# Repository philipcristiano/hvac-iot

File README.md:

# hvac-iot
IoT system for HVAC control

## Develop

Get Arduino CLI

See `.github/workflows/Arduino_Sensor.yml` for the most up to date steps

### Compile

```
arduino-cli compile --fqbn adafruit:samd:adafruit_feather_m0 Sensor

```

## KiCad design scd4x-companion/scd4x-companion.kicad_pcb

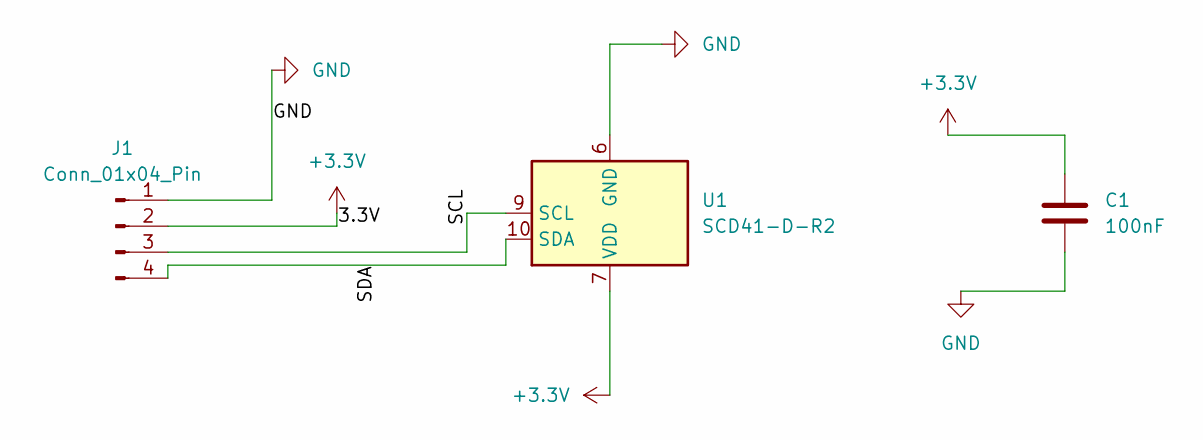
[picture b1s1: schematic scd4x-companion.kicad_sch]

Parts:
C1: 100nF; C_0603_1608Metric
J1: Conn_01x04_Pin; 1x04
U1: SCD41-D-R2; Sensirion_SCD4x-1EP_10.1x10.1mm_P1.25mm_EP4.8x4.8mm

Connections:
+3.3V: C1.1, J1.2, U1.7 (VDD), U1.19 (VDD)
/SCL: J1.3, U1.9 (SCL)
/SDA: J1.4, U1.10 (SDA)
GND: C1.2, J1.1, U1.6 (GND), U1.20 (GND), U1.21 (GND)

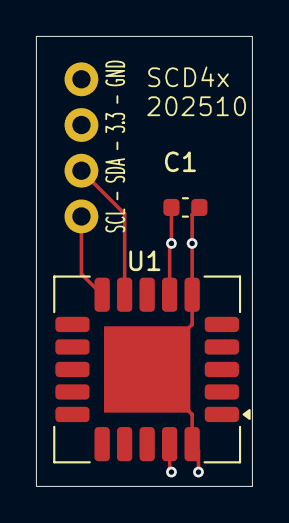
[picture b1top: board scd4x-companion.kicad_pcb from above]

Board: 2 copper layers, 12.0 x 25.0 mm, 3 parts (0 on the bottom side), 4 nets.

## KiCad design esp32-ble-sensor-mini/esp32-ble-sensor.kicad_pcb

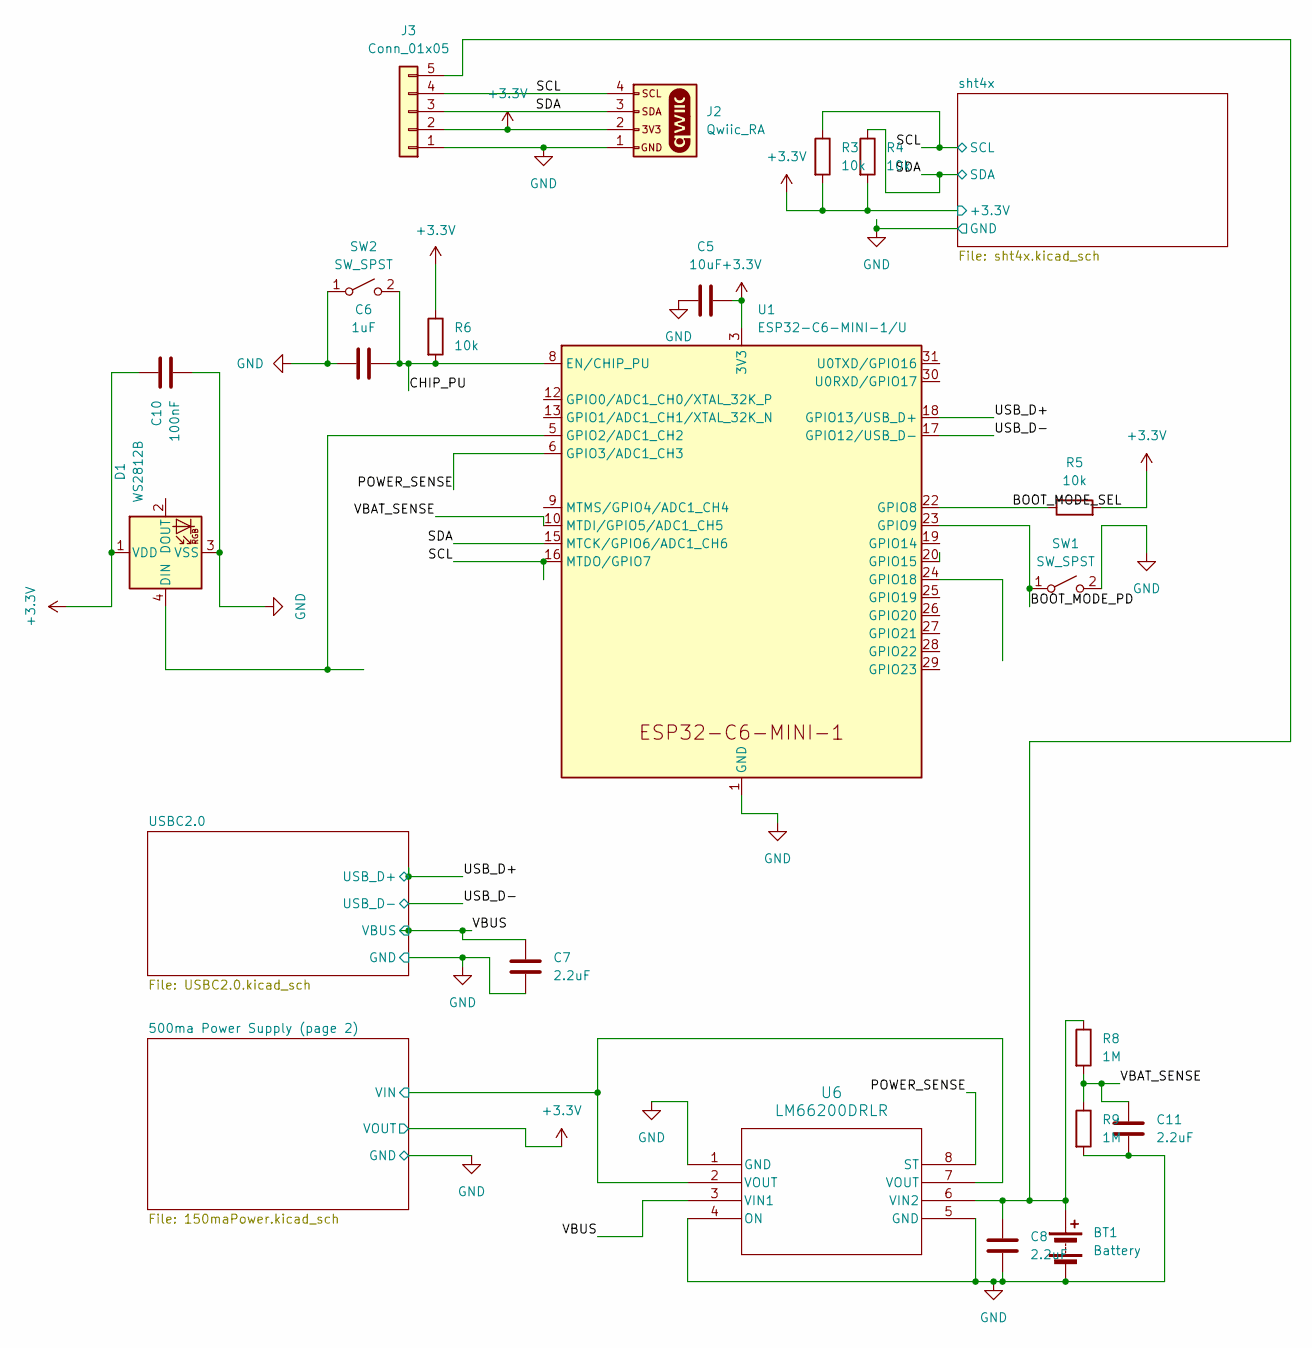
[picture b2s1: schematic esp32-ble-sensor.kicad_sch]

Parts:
BT1: Battery; BatteryHolder_Keystone_1042_1x18650
C5: 10uF; C_1206_3216Metric
C6: 1uF; C_1206_3216Metric
C7, C8, C11: 2.2uF; C_1206_3216Metric
C10: 100nF; C_0603_1608Metric
D1: WS2812B; LED_WS2812B_PLCC4_5.0x5.0mm_P3.2mm
J2: Qwiic_RA; JST_SMD_1.0mm-4_Black
J3: Conn_01x05; 1x05_Castellated
R3, R4, R5, R6: 10k; R_0603_1608Metric
R8, R9: 1M; R_0603_1608Metric
SW1, SW2: SW_SPST; SW_TS18-5-17-SL-260-SMT-TR
U1: ESP32-C6-MINI-1/U; ESP32-C6-MINI-1
U6: LM66200DRLR; SOT-5X3_DRL_TEX

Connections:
+3.3V: C5.2, C10.1, D1.1 (VDD), J2.2, J3.2, R3.2, R4.2, R5.2, R6.1, U1.3 (3V3); also elsewhere on the board
/500ma Power Supply (page 2)/VIN: U6.2 (VOUT), U6.7 (VOUT); also elsewhere on the board
/BOOT_MODE_PD: SW1.1 (A), U1.23 (GPIO9)
/BOOT_MODE_SEL: R5.1, U1.22 (GPIO8)
/CHIP_PU: C6.1, R6.2, SW2.2 (B), U1.8 (EN/CHIP_PU)
/POWER_SENSE: U1.6 (GPIO3/ADC1_CH3), U6.8 (ST)
/SCL: J2.4, J3.4, R3.1, U1.16 (MTDO/GPIO7); also elsewhere on the board
/SDA: J2.3, J3.3, R4.1, U1.15 (MTCK/GPIO6/ADC1_CH6); also elsewhere on the board
/USB_D+: U1.18 (GPIO13/USB_D+); also elsewhere on the board
/USB_D-: U1.17 (GPIO12/USB_D-); also elsewhere on the board
/VBAT_SENSE: C11.1, R8.2, R9.1, U1.10 (MTDI/GPIO5/ADC1_CH5)
/VBUS: C7.1, U6.3 (VIN1); also elsewhere on the board
GND: BT1.2 (-), C5.1, C6.2, C7.2, C8.2, C10.2, C11.2, D1.3 (VSS), J2.1, J3.1, R9.2, SW1.2 (B), SW2.1 (A), U1.1 (GND), U1.2 (GND), U1.11 (GND), U1.14 (GND), U1.36 (GND), U1.37 (GND), U1.38 (GND), U1.39 (GND), U1.40 (GND), U1.41 (GND), U1.42 (GND), U1.43 (GND), U1.44 (GND), U1.45 (GND), U1.46 (GND), U1.47 (GND), U1.48 (GND), U1.49 (GND), U1.50 (GND), U1.51 (GND), U1.52 (GND), U1.53 (GND), U6.1 (GND), U6.4 (ON), U6.5 (GND); also elsewhere on the board
unnamed: BT1.1 (+), C8.1, J3.5, R8.1, U6.6 (VIN2)
unnamed: D1.4 (DIN), U1.5 (GPIO2/ADC1_CH2)

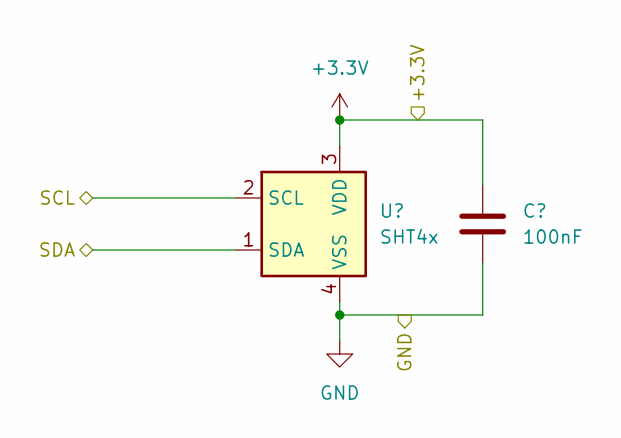
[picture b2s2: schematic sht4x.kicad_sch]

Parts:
C1: 100nF; C_0603_1608Metric
U2: SHT4x; Sensirion_DFN-4_1.5x1.5mm_P0.8mm_SHT4x_NoCentralPad

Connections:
+3.3V: C1.1, U2.3 (VDD); also elsewhere on the board
/SCL: U2.2 (SCL); also elsewhere on the board
/SDA: U2.1 (SDA); also elsewhere on the board
GND: C1.2, U2.4 (VSS); also elsewhere on the board

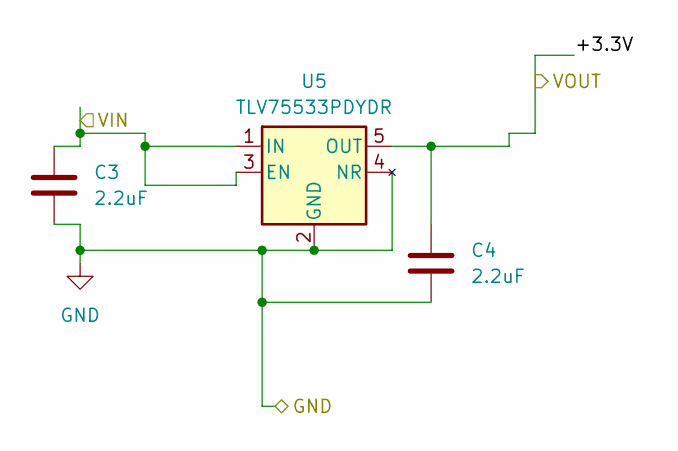
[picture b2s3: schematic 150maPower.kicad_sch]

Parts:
C3, C4: 2.2uF; C_1206_3216Metric
U5: TLV75533PDYDR; SOT-23-5

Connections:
+3.3V: C4.1, U5.5 (OUT); also elsewhere on the board
/500ma Power Supply (page 2)/VIN: C3.1, U5.1 (IN), U5.3 (EN); also elsewhere on the board
GND: C3.2, C4.2, U5.2 (GND), U5.4 (NR); also elsewhere on the board

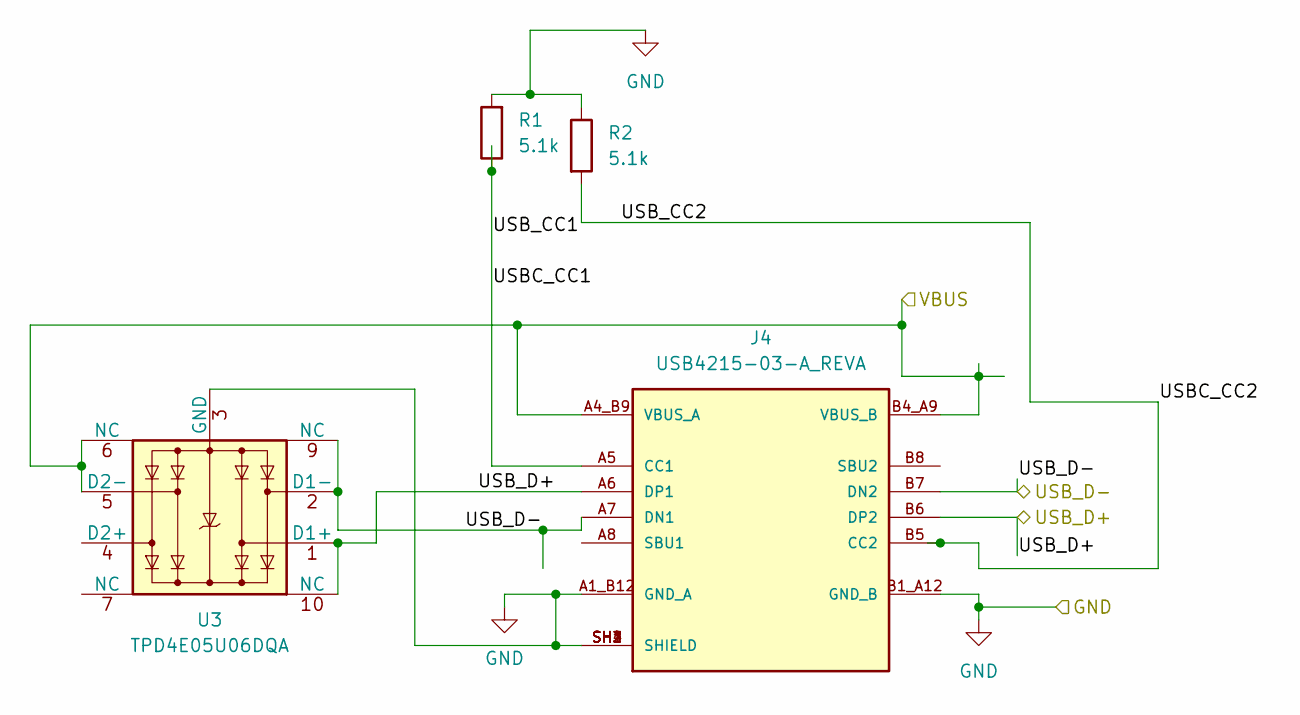
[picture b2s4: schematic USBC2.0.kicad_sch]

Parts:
J4: USB4215-03-A_REVA; GCT_USB4215-03-A_REVA; PARTREV A
R1, R2: 5.1k; R_0603_1608Metric
U3: TPD4E05U06DQA; USON-10_2.5x1.0mm_P0.5mm

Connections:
/USBC2.0/USBC_CC1: J4.A5 (CC1), R1.1
/USBC2.0/USBC_CC2: J4.B5 (CC2), R2.2
/USB_D+: J4.A6 (DP1), J4.B6 (DP2), U3.1 (D1+), U3.10 (NC); also elsewhere on the board
/USB_D-: J4.A7 (DN1), J4.B7 (DN2), U3.2 (D1-), U3.9 (NC); also elsewhere on the board
/VBUS: J4.A4_B9 (VBUS_A), J4.B4_A9 (VBUS_B), U3.5 (D2-), U3.6 (NC); also elsewhere on the board
GND: J4.A1_B12 (GND_A), J4.B1_A12 (GND_B), J4.SH1 (SHIELD), J4.SH2 (SHIELD), J4.SH3 (SHIELD), J4.SH4 (SHIELD), R1.2, R2.1, U3.3 (GND), U3.8 (GND); also elsewhere on the board

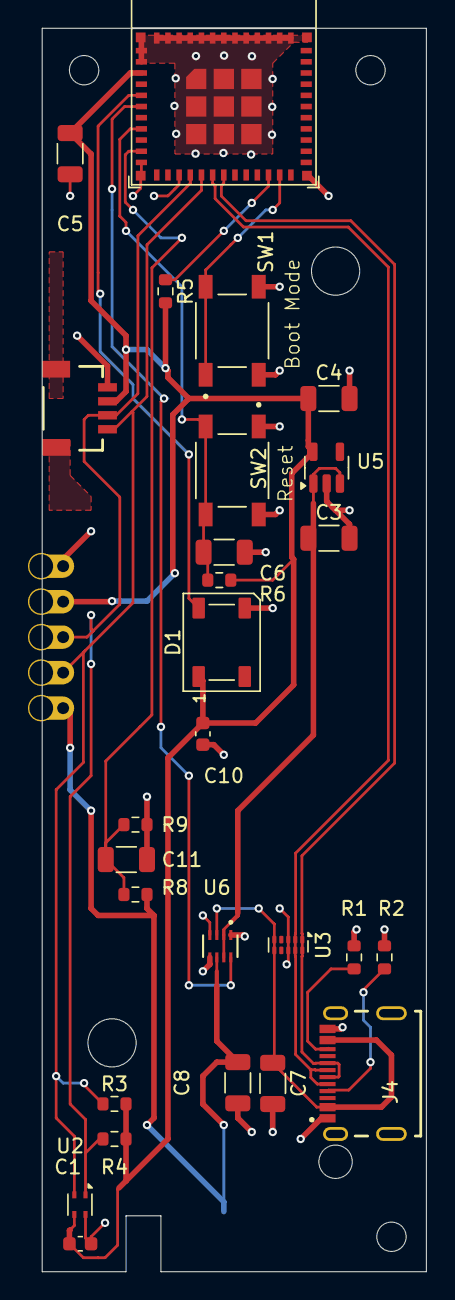
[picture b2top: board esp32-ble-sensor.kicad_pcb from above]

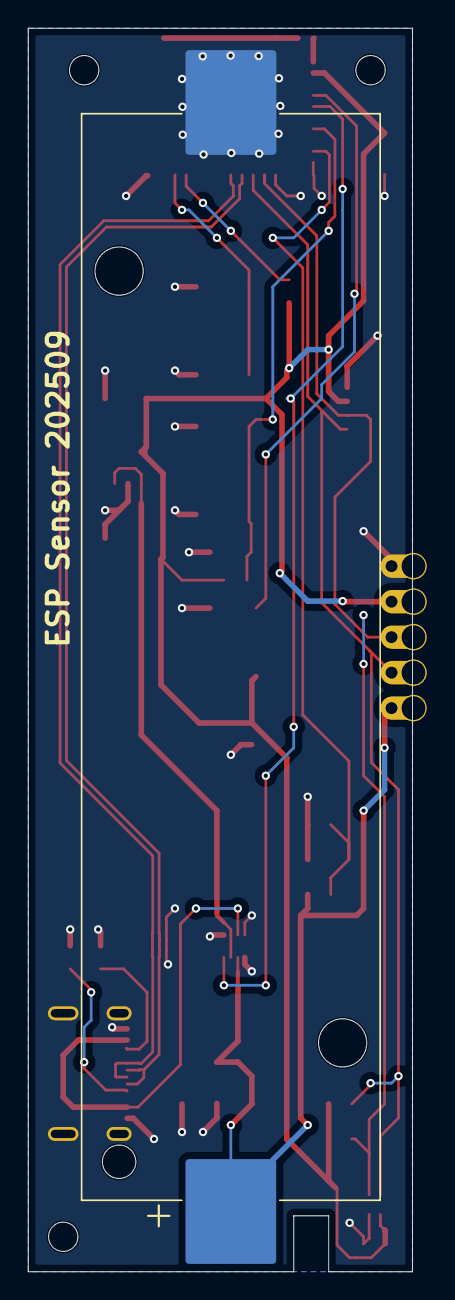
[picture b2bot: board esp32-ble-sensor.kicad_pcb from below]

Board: 2 copper layers, 27.5 x 89.0 mm, 29 parts (2 on the bottom side), 17 nets.

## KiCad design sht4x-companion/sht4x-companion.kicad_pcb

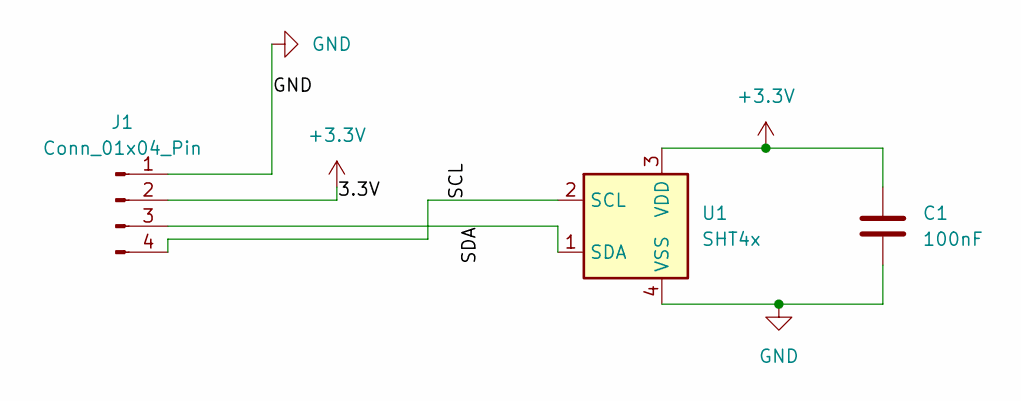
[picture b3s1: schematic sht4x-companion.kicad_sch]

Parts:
C1: 100nF; C_0603_1608Metric
J1: Conn_01x04_Pin; 1x04
U1: SHT4x; Sensirion_DFN-4_1.5x1.5mm_P0.8mm_SHT4x_NoCentralPad

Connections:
+3.3V: C1.1, J1.2, U1.3 (VDD)
/SCL: J1.4, U1.2 (SCL)
/SDA: J1.3, U1.1 (SDA)
GND: C1.2, J1.1, U1.4 (VSS)

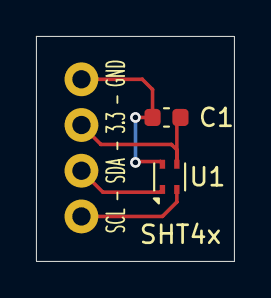
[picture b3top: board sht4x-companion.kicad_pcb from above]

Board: 2 copper layers, 11.0 x 12.5 mm, 3 parts (0 on the bottom side), 4 nets.

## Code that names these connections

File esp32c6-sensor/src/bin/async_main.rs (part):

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    esp_alloc::heap_allocator!(size: 72 * 1024);
    let i2c = master::I2c::new(peripherals.I2C0, master::Config::default())
        .unwrap()
        .with_scl(peripherals.GPIO7)
        .with_sda(peripherals.GPIO6)
        .into_async();

    use embassy_embedded_hal::shared_bus::asynch::i2c::I2cDevice;
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    //let timer0 = esp_hal::timer::systimer::SystemTimer::new(peripherals.SYSTIMER);

    let mut adc1_config = esp_hal::analog::adc::AdcConfig::new();
    let analog_pin1 = peripherals.GPIO5;
    let mut pin1 = adc1_config.enable_pin_with_cal::<_, AdcCalCurve<_>>(
        analog_pin1,
        esp_hal::analog::adc::Attenuation::_11dB,
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    let green_light = RGB8 { r: 0, g: 5, b: 0 };
    let disable_light = RGB8 { r: 0, g: 0, b: 0 };
    use esp_hal::time::Rate;
    let led_pin = peripherals.GPIO2;

    let rmt = Rmt::new(peripherals.RMT, Rate::from_mhz(80)).unwrap();
    let rmt_channel = rmt.channel0;
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
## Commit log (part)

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2021-03-28 Start trying to use CLI
2021-03-28 workflow: Compile Sensor
2021-04-28 Remove sgp30: not using it for this yet
2021-04-28 sensor: Write more data via binary
2021-04-28 Fix build process
2021-04-28 wip: Trying to build binary rf message
2021-08-07 Adjust frequency
2021-08-07 Working binary sensor
    Nicer additions of sensors to the message line
2021-08-22 wip: Start pm25aqi sensor
    https://learn.adafruit.com/pm25-air-quality-sensor/arduino-code
2021-08-24 Start hub
2021-08-24 pm25aqi: Send data via RF
2021-08-24 Build hub
2021-08-26 hub: Add ethernet lib to build
2022-01-22 Add in WIP kicad thermostat
2022-02-01 thermostat: Use A4 for bat voltage detection
    This matches what is done in the current sketch / prototypes to avoid
    overloading with the display featherwing
2022-02-01 hub: Fix lint errors
2022-02-03 thermostat: Add bootstrap programming headers
2022-02-16 thermostat: Connect and label pins
2022-02-19 CI kicad file
2022-02-20 thermostat: Fix GND power pin designation
2022-02-20 thermostat: Link libraries
2022-02-20 libraries: Migrate to kicad 6
2022-02-20 thermostat: Link symbols
2022-02-20 thermostat: Fix lines
2022-02-20 thermostat: Use switch
2025-02-07 Start rust version of a sensor
2025-02-13 esp32h2-sensor: Read from SHT40 sensor
    And print it to the log.
2025-02-16 wip: Able to send temp and humidty
    The values are wrong, and sometimes wifi config doesn't get fully set
    and it appears nothing will work... but a power reset shows it working
2025-02-16 wip: I think things are crashing, but I can load this onto the mc
2025-07-12 esp32-h2 working
    But no sleep for h2
2025-07-15 esp32-c6-sensor v0.1 202507
2025-07-28 Convert from h2 to c6 module
2025-08-02 Semi working sensor... testing flash loop
2025-08-02 esp-hal 1.0.0-rc.0
2025-08-02 esp32c6: Sensor working for temp, humidity, battery
    And sleeps!
    Need to confirm battery usage and life
2025-08-11 Fix warnings
2025-08-11 chore: Remove older workflow files
    These are not longer needed
2025-08-11 chore: Update flake
2025-08-11 Add renovate
2025-08-11 Sync kicad
2025-08-11 Ignore mac finder files
2025-08-11 workflow: Run in correct directory
    Match -, get updated workflow
2025-08-12 Move panic handler up
    See if it fixes the github build
2025-08-12 Install target
2025-08-12 fix(deps): update rust crate defmt to v1
2025-08-12 Disable tests
    Which are broken on github and there are no tests
2025-08-15 fix(deps): update rust crate embassy-sync to v0.7.1
2025-08-15 fix(deps): update rust crate embassy-sync to v0.7.1 (#11)
2025-08-16 fix(deps): update rust crate bt-hci to 0.4.0
2025-08-16 fix(deps): update rust crate embassy-executor to 0.8.0
2025-08-18 chore(deps): lock file maintenance
2025-08-18 chore(deps): lock file maintenance (#12)
2025-08-20 fix(deps): update rust crate heapless to 0.9.0
2025-08-20 fix(deps): update rust crate heapless to 0.9.0 (#13)
2025-08-25 chore(deps): lock file maintenance (#14)
2025-08-27 fix(deps): update rust crate embassy-futures to v0.1.2
2025-08-27 fix(deps): update rust crate embassy-sync to v0.7.2
2025-08-27 fix(deps): update rust crate embassy-futures to v0.1.2 (#15)
2025-08-27 fix(deps): update rust crate embassy-sync to v0.7.2 (#16)
2025-08-27 fix(deps): update rust crate embassy-embedded-hal to 0.5.0
2025-08-27 fix(deps): update rust crate embassy-embedded-hal to 0.5.0 (#17)
2025-08-28 fix(deps): update rust crate embassy-executor to 0.9.0
2025-08-28 fix(deps): update rust crate embassy-time to 0.5.0
2025-09-26 fix(deps): update rust crate bt-hci to 0.6.0
2025-10-14 shtx companion 202510
2025-10-14 chore: Update dependencies
2025-10-14 esp32 sensor 202509
2025-10-15 chore: remove deprecated/removed darwin req for flakes
2025-10-15 scd4x companion 202510
    Child board to hold a scd4x sensor
2025-10-15 chore(deps): update rust crate log to v0.4.28
2025-10-15 chore(deps): update rust crate smart-leds-trait to v0.3.2
2025-10-15 fix(deps): update rust crate esp-alloc to 0.9.0
2025-10-30 fix(deps): update rust crate esp-radio to 0.17.0
2025-11-18 fix: Update to get LEDs working again
2025-11-18 Fix missing test config for embedded
    Things don't work on embedded with all targets on non-embedded system
2025-11-18 chore(deps): update agenthunt/conventional-commit-checker-action action to v2.0.1
2025-11-18 fix(deps): update rust crate embedded-io to 0.7.0
2025-11-18 fix(deps): update rust crate esp-bootloader-esp-idf to 0.4.0
2025-11-18 fix(deps): update rust crate esp-println to 0.16.0
2025-11-18 fix(deps): update rust crate trouble-host to 0.5.0
2025-11-18 chore(deps): update agenthunt/conventional-commit-checker-action action to v2.0.1 (#31)
2025-11-18 fix(deps): update rust crate embedded-io to 0.7.0 (#22)
2025-11-18 fix(deps): update rust crate esp-bootloader-esp-idf to 0.4.0 (#27)
2025-11-18 fix(deps): update rust crate esp-println to 0.16.0 (#28)
2025-11-18 chore(deps): lock file maintenance (#20)
2025-11-18 fix(deps): update rust crate trouble-host to 0.5.0 (#21)
2025-11-19 fix(deps): update rust crate embedded-io-async to 0.7.0
2025-11-19 fix(deps): update rust crate embedded-io-async to 0.7.0 (#23)
2025-11-24 chore(deps): lock file maintenance (#32)
2025-11-24 chore(deps): update rust crate trouble-host to v0.5.1
2025-11-24 chore(deps): update rust crate trouble-host to v0.5.1 (#33)
2025-12-01 chore(deps): lock file maintenance (#34)
2025-12-03 chore(deps): update rust crate log to v0.4.29
2025-12-03 chore(deps): update rust crate log to v0.4.29 (#35)
2025-12-08 chore(deps): lock file maintenance (#36)
2025-12-15 chore(deps): lock file maintenance (#37)
2025-12-22 chore(deps): lock file maintenance (#38)
2025-12-29 chore(deps): lock file maintenance (#39)
2026-01-05 chore(deps): lock file maintenance (#40)
2026-01-12 chore(deps): lock file maintenance (#42)
2026-01-19 chore(deps): lock file maintenance (#43)
2026-01-26 chore(deps): lock file maintenance (#44)
2026-02-02 chore(deps): lock file maintenance (#45)
2026-02-09 chore(deps): lock file maintenance (#46)
2026-02-16 chore(deps): lock file maintenance (#48)
2026-02-23 chore(deps): lock file maintenance (#49)
2026-03-02 chore(deps): lock file maintenance (#50)
2026-03-09 chore(deps): lock file maintenance (#51)
2026-03-16 chore(deps): lock file maintenance (#52)
2026-03-31 chore(deps): update rust crate embassy-time to v0.5.1
2026-03-31 chore(deps): update rust crate embassy-time to v0.5.1 (#53)
2026-04-01 fix(deps): update rust crate smoltcp to 0.13.0
2026-04-01 fix(deps): update rust crate smoltcp to 0.13.0 (#57)
2026-04-01 fix(deps): update rust crate scd4x to 0.5.0
2026-04-01 fix(deps): update rust crate scd4x to 0.5.0 (#58)
2026-04-06 chore(deps): lock file maintenance (#59)
2026-04-06 fix(deps): update rust crate embassy-embedded-hal to 0.6.0
2026-04-06 fix(deps): update rust crate embassy-sync to 0.8.0
2026-04-06 chore(deps): lock file maintenance (#60)
